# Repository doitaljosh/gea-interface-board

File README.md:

KiCAD Board Files for an open source adapter that allows hacking and protyping 
with GE appliances.

### Note: these haven't been tested or produced.

They are based off of GE's official implementation. I've reverse engineered an 
interface on an oven board, and this is essentially a half-duplex to full-duplex 
UART converter. It can talk to two appliances at once, as it has two channels.
A smaller, single channel variant is in the works.

#### RJ45 port pinout:
1. GND
2. GEA_E (half-duplex 19200 baud)
3. 9-14VDC
4. GEA2_RXD (full-duplex 230400 baud)
5. GEA2_TXD
6. 5V
7. NC
8. NC

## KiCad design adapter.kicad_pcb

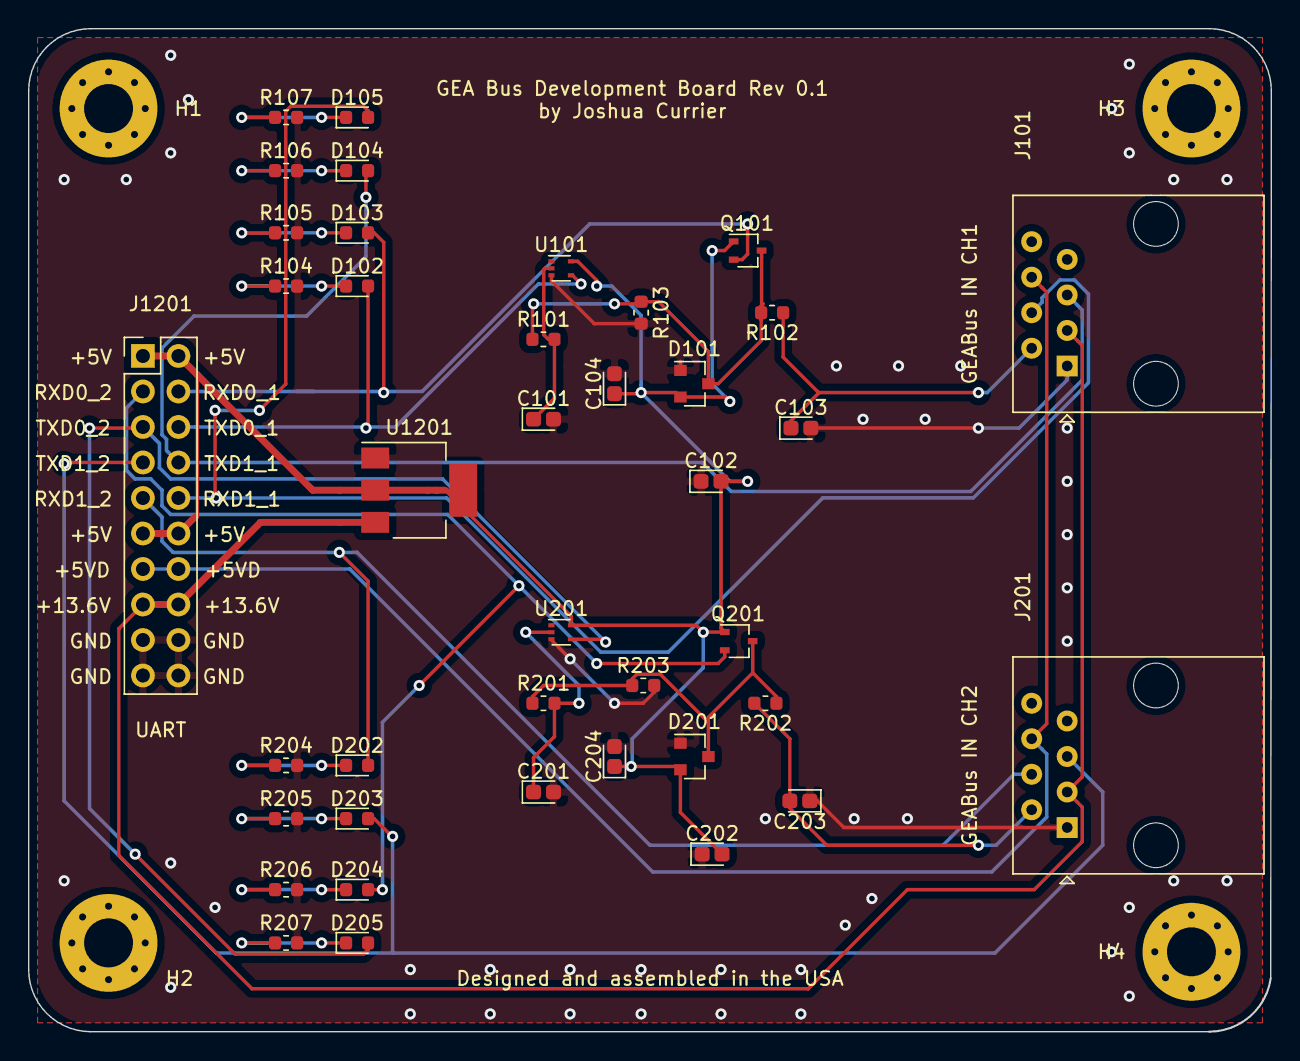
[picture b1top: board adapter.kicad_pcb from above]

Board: 2 copper layers, 88.9 x 71.7 mm, 44 parts (0 on the bottom side), 26 nets.

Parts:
C101, C102, C103, C104, C201, C202, C203, C204: 0.1u; CP_EIA-1608-10_AVX-L
D101, D201: BAV99; SOT-23
D102, D103, D104, D105, D202, D203, D204, D205: LED; LED_0603_1608Metric
H1, H2, H3, H4: MountingHole_3.5mm_Pad_Via
J101: GEABus IN CH1; RJ45_Amphenol_54602-x08_Horizontal
J201: GEABus IN CH2; RJ45_Amphenol_54602-x08_Horizontal
J1201: UART; PinHeader_2x10_P2.54mm_Vertical
Q101, Q201: DTA143X; SOT-323_SC-70
R101, R201: 47k; R_0603_1608Metric
R102, R202: 120; R_0603_1608Metric
R103, R203: 22k; R_0603_1608Metric
R104, R105, R106, R107, R204, R205, R206, R207: 330; R_0603_1608Metric
U101, U201: 74LVC1GU04DRL; SOT-553
U1201: AMS1117-5.0; SOT-223-3_TabPin2

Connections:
+5V: C102.2, C104.1, C202.2, C204.1, D101.2, D201.2, J1201.1, J1201.2, J1201.11, J1201.12, Q101.1, Q201.1, U101.5, U201.5, U1201.2
GND: C101.2, C102.1, C103.2, C104.2, C201.2, C202.1, C203.1, C204.2, D101.1, D201.1, J101.1, J201.1, J1201.17, J1201.18, J1201.19, J1201.20, R103.2, R104.2, R105.2, R106.2, R107.2, R203.2, R204.2, R205.2, R206.2, R207.2, U101.3, U201.3, U1201.1
unnamed: C101.1, R101.2, U101.2
unnamed: C103.1, J101.2, R102.1
unnamed: C201.1, R201.2, U201.2
unnamed: C203.2, J201.2, R202.2
unnamed: D101.3, Q101.3, R101.1, R102.2, R103.1
unnamed: D102.1, R104.1
unnamed: D102.2, J1201.6, U101.4
unnamed: D103.1, R105.1
unnamed: D103.2, J1201.4, Q101.2
unnamed: D104.1, R106.1
unnamed: D104.2, J101.5, J1201.8
unnamed: D105.1, R107.1
unnamed: D105.2, J101.4, J1201.10
unnamed: D201.3, Q201.3, R201.1, R202.1, R203.1
unnamed: D202.1, R204.1
unnamed: D202.2, J201.4, J1201.9
unnamed: D203.1, R205.1
unnamed: D203.2, J201.5, J1201.7
unnamed: D204.1, R206.1
unnamed: D204.2, J1201.3, Q201.2
unnamed: D205.1, R207.1
unnamed: D205.2, J1201.5, U201.4
unnamed: J101.3, J201.3, J1201.15, J1201.16, U1201.3
unnamed: J101.6, J201.6, J1201.13, J1201.14
